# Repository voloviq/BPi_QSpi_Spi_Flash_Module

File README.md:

# BPi_QSpi_Spi_Flash_Module
Support board for QSpi and Spi Flash memories

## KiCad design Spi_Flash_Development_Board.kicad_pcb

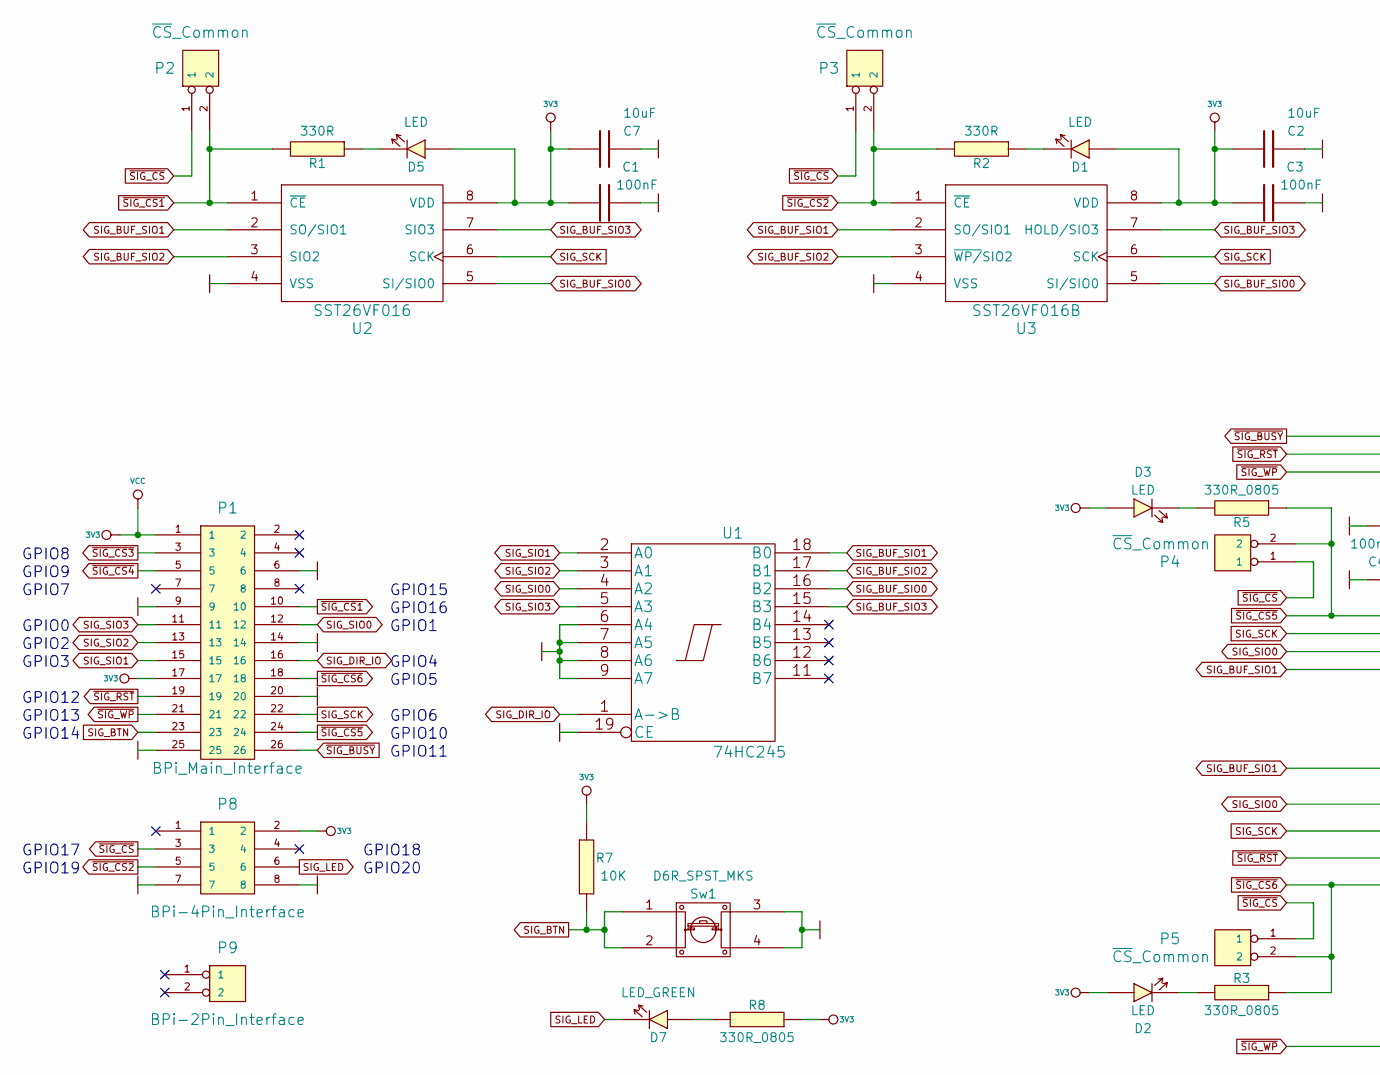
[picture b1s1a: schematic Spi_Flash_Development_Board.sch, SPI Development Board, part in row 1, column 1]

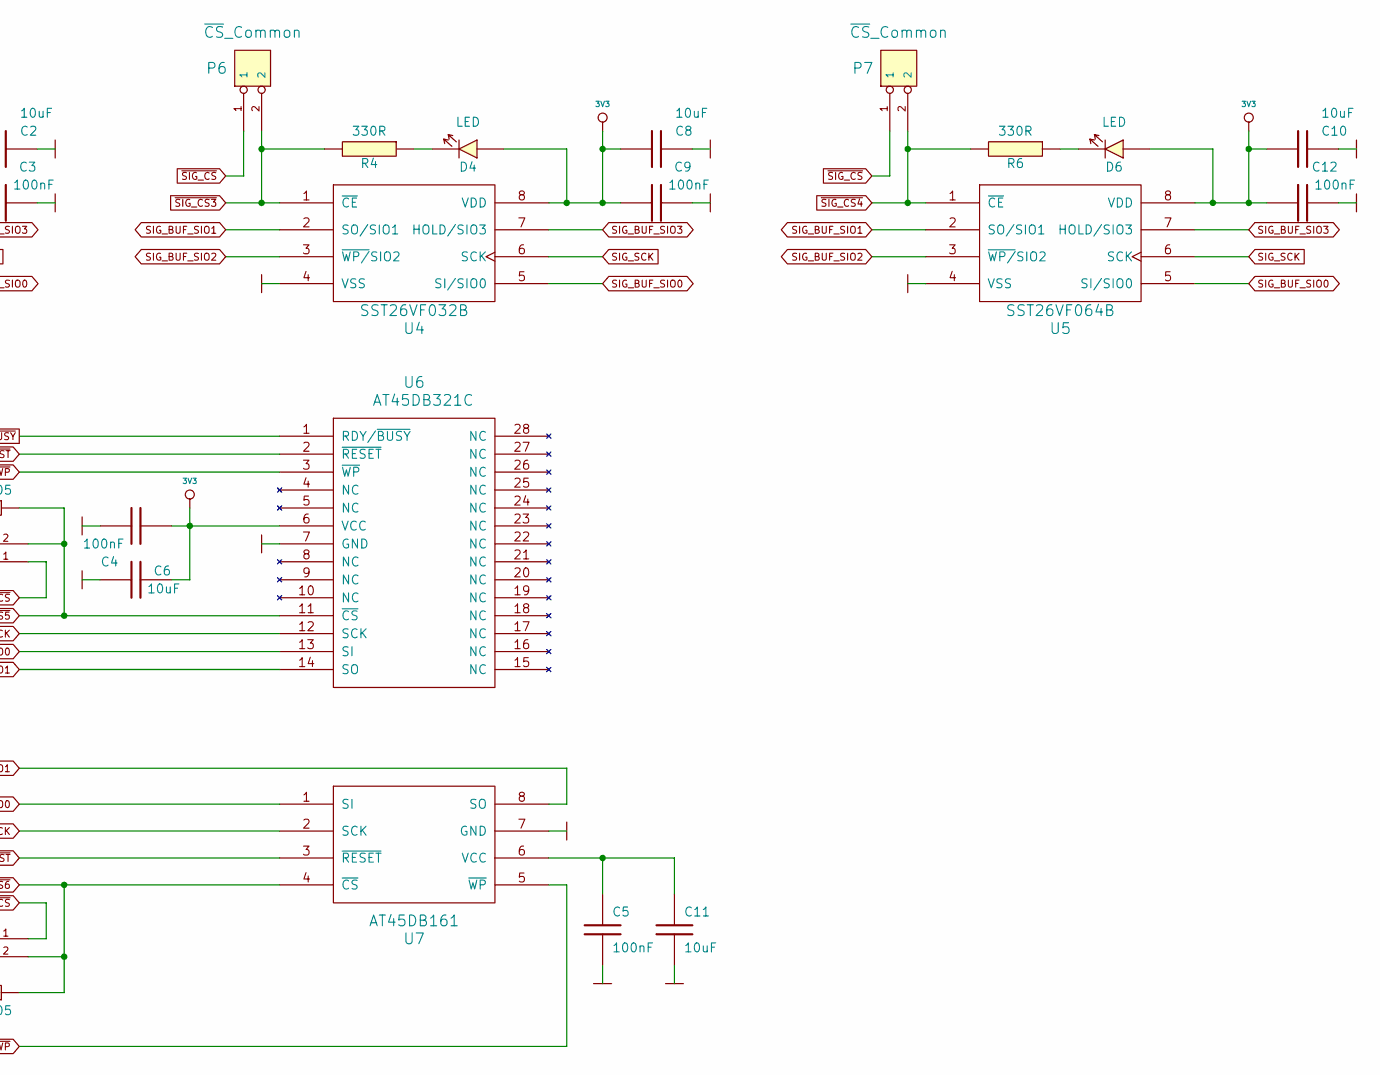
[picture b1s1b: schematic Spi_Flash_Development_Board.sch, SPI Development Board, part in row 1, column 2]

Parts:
C1, C3, C4, C5, C9, C12: 100nF; 100nF_0805
C2, C6, C7, C8, C10, C11: 10uF; 10uF_0805
D1, D2, D3, D4, D5, D6: LED; LED_KP-2012HD_SM0805
D7: LED_GREEN; LED_KP-2012SGD_SM0805
P1: BPi_Main_Interface; Goldpin_13_2_2_54mm
P2, P3, P4, P5, P6, P7: ~CS~_Common; Goldpin_2_2_54mm_With_Strip
P8: BPi-4Pin_Interface; Goldpin_4_2_2_54mm
P9: BPi-2Pin_Interface; Goldpin_2_2_54mm
R1, R2, R4, R6: 330R; 330R_0805
R3, R5, R8: 330R_0805
R7: 10K; 10k_0805
Sw1: D6R_SPST_MKS; D6_SPST_MKS
U1: 74HC245; 74HC245_TSSOP20
U2: SST26VF016; SST26VF016_SOIC
U3: SST26VF016B; SST26VF016B_SOIC
U4: SST26VF032B; SST26VF032B_SOIC
U5: SST26VF064B; SST26VF064B_SOIC
U6: AT45DB321C; AT45DB321C_TSSOP
U7: AT45DB161; AT45DB161D_SOIC

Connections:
3V3: C1.1, C2.2, C3.1, C4.1, C6.2, C7.2, C8.2, C9.1, C10.2, C12.1, D1.1 (A), D2.1 (A), D3.1 (A), D4.1 (A), D5.1 (A), D6.1 (A), P1.1, P1.17, P8.2, R7.1, R8.1, U1.20 (VCC), U2.8 (VDD), U3.8 (VDD), U4.8 (VDD), U5.8 (VDD), U6.6 (VCC)
GND: C1.2, C2.1, C3.2, C4.2, C5.2, C6.1, C7.1, C8.1, C9.2, C10.1, C11.2, C12.2, P1.6, P1.9, P1.14, P1.20, P1.25, P8.7, P8.8, Sw1.3, Sw1.4, U1.6 (A4), U1.7 (A5), U1.8 (A6), U1.9 (A7), U1.10 (GND), U1.19 (CE), U2.4 (VSS), U3.4 (VSS), U4.4 (VSS), U5.4 (VSS), U6.7 (GND), U7.7 (GND)
unnamed: C5.1, C11.1, U7.6 (VCC)
unnamed: D1.2 (K), R2.1
unnamed: D2.2 (K), R3.2
unnamed: D3.2 (K), R5.2
unnamed: D4.2 (K), R4.1
unnamed: D5.2 (K), R1.1
unnamed: D6.2 (K), R6.1
unnamed: D7.1 (A), R8.2
SIG_BTN: P1.23, R7.2, Sw1.1, Sw1.2
SIG_BUF_SIO0: U1.16 (B2), U2.5 (SI/SIO0), U3.5 (SI/SIO0), U4.5 (SI/SIO0), U5.5 (SI/SIO0)
SIG_BUF_SIO1: U1.18 (B0), U2.2 (SO/SIO1), U3.2 (SO/SIO1), U4.2 (SO/SIO1), U5.2 (SO/SIO1), U6.14 (SO), U7.8 (SO)
SIG_BUF_SIO2: U1.17 (B1), U2.3 (SIO2), U3.3 (~WP/~SIO2), U4.3 (~WP/~SIO2), U5.3 (~WP/~SIO2)
SIG_BUF_SIO3: U1.15 (B3), U2.7 (SIO3), U3.7 (HOLD/SIO3), U4.7 (HOLD/SIO3), U5.7 (HOLD/SIO3)
SIG_DIR_IO: P1.16, U1.1 (A->B)
SIG_LED: D7.2 (K), P8.6
SIG_SCK: P1.22, U2.6 (SCK), U3.6 (SCK), U4.6 (SCK), U5.6 (SCK), U6.12 (SCK), U7.2 (SCK)
SIG_SIO0: P1.12, U1.4 (A2), U6.13 (SI), U7.1 (SI)
SIG_SIO1: P1.15, U1.2 (A0)
SIG_SIO2: P1.13, U1.3 (A1)
SIG_SIO3: P1.11, U1.5 (A3)
~SIG_BUSY: P1.26, U6.1 (RDY/~BUSY)
~SIG_CS: P2.1, P3.1, P4.1, P5.1, P6.1, P7.1, P8.3
~SIG_CS1: P1.10, P2.2, R1.2, U2.1 (~CE)
~SIG_CS2: P3.2, P8.5, R2.2, U3.1 (~CE)
~SIG_CS3: P1.3, P6.2, R4.2, U4.1 (~CE)
~SIG_CS4: P1.5, P7.2, R6.2, U5.1 (~CE)
~SIG_CS5: P1.24, P4.2, R5.1, U6.11 (~CS)
~SIG_CS6: P1.18, P5.2, R3.1, U7.4 (~CS)
~SIG_RST: P1.19, U6.2 (~RESET), U7.3 (~RESET)
~SIG_WP: P1.21, U6.3 (~WP), U7.5 (~WP)

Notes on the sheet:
GPIO8
GPIO9
GPIO0
GPIO2
GPIO3
GPIO12
GPIO13
GPIO14
GPIO11
GPIO10
GPIO6
GPIO5
GPIO4
GPIO1
GPIO16
GPIO17
GPIO18
GPIO19
GPIO20
GPIO7
GPIO15

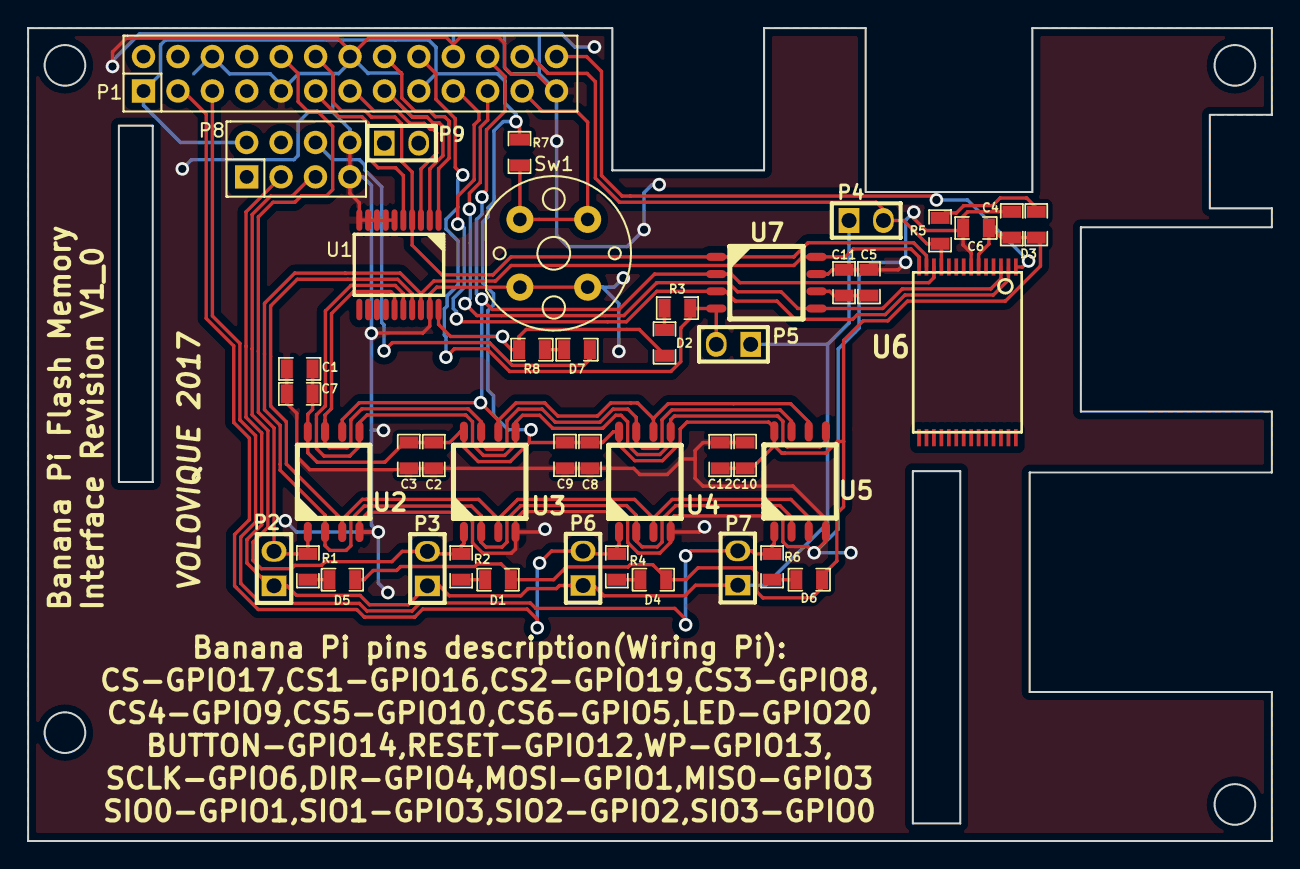
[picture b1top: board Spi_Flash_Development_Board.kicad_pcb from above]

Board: 2 copper layers, 91.8 x 60.0 mm, 44 parts (0 on the bottom side), 32 nets.

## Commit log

2017-01-25 Initial revision
2017-01-26 RC1 of Banana Pi Flash Memory Interface
2017-01-27 Final verion of board V1_0. Prototype started.
